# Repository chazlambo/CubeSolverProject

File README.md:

# CubeSolver

A self-contained Rubik's Cube solving robot: six stepper-driven faces, two servo
grippers on a moving ring, eighteen color sensors, an on-board Kociemba
two-phase solver, and a 320×240 display. Scan, solve, execute — no PC involved.

Everything here is one person's design: mechanical (SolidWorks), electrical
(KiCad), and firmware (Teensy 4.1).

---

## Status

**Working:** full autonomous scan → solve → execute cycle, driven from the
panel menu: the five Modes (Scramble Solve, Idle, Demo, Step Solve, Patterns),
on-panel tuning with defaults in source and overrides in EEPROM, a hardware jog
page, live sensor diagnostics, an EEPROM fault log and lifetime stats. The
display stays live during scan and solve, the abort chord works throughout,
encoder faults are detected and handled, a scan is validated piece-by-piece
with automatic repair, and color classification carries a per-sensor
confidence.

**Known unfinished:**
- `VirtualCube::rebuildFromCubeArray()` — still labeled `UNFINISHED NEEDS
  DEBUGGING` in its header, but the body is live and the firmware now relies
  on it (Cube State and pattern completion refresh the color array through
  it). The stale part is the label, not the code; it has no rollback on
  failure, which no current caller needs.
- Color sensor board 2, sensor 2 has a **dead green channel** — it reads exactly
  `0` for all six sticker colors in every archived calibration run. The firmware
  now detects this (`ColorSensor::checkSensorHealth`) but it is a hardware fault.
- Face steppers run without an acceleration ramp (`MultiStepper` is constant
  speed by design). Left as-is deliberately — a ramp would slow the solve.

---

## Which sketch do I flash?

**`Code/Main Code/CubeSolver/CubeSolver.ino`** — that's the program.

Everything under `Code/Test Code/` is bring-up and calibration tooling. The ones
still worth keeping:

| Sketch | Purpose |
|---|---|
| `Test Code/Bench_Tune` | Headless Serial protocol for scripted tuning: moves, parameters, every encoder before/after each move. Driven by `Code/tools/bench.py` |
| `Test Code/Actuator_Test` | Serial menu for manual moves and jam-recovery testing |
| `Test Code/Test_Motor_Calibrate` | Motor encoder calibration (also Settings → Calibration → Motor Positions) |
| `Test Code/Test_Color_Calibrate` | Color calibration (also Settings → Calibration → Color Sensors) |
| `Test Code/I2C_Search` | Bus scanner — genuinely useful on a five-mux rig |
| `Test Code/Test_Menu` | Menu, wheel and panel bench test — see below |

**`Test Code/Test_Menu`** drives the same `CubeMenu` and `CubeDisplay` the
firmware does, so anything that feels wrong there feels wrong in the firmware.
It runs no scan, solve or calibration. It does move real hardware from three
places: **Load** / **Eject**, the **Actuators** page (every servo and ring
position, each face motor and both whole-cube rotations, one part at a time),
and Diagnostics → Tuning → Servos, which drives a horn to each value as you
dial it. Everything under `Screens` is drawing only.

It also carries a `Screens` submenu that draws each operation screen (scan step
rows, calibration color chips, the solve progress bar, the error look) from
canned data, so the panel can be judged and photographed in seconds instead of
by running a 40-second scan to check one label. `Input Report` is a live
readout of the wheel count and every button — the fastest way to spot a flaky
encoder or a dead button.

It runs in the simulator too, with no machine at all:

```sh
cmake -S Code/sim -B Code/sim/build-test -DSIM_SKETCH=Test_Menu
cmake --build Code/sim/build-test -j && ./Code/sim/build-test/cubesim
```

`Test Code/_Archive/` does not compile against the current tree (it includes a
`Cube.h` that no longer exists). Git history is the archive.

---

## Build

**Board:** Teensy 4.1. Not a 4.0 — the solver's lookup tables alone are 4.14 MiB,
which is 214% of a 4.0's flash, and pins 40/41 don't exist on a 4.0.

**Toolchain:** Arduino IDE + Teensyduino.

> **TODO:** record the exact Arduino IDE and Teensyduino versions you build with,
> plus CPU speed and USB type from the Tools menu.

**Sketchbook layout — this is the non-obvious step.** `Code/libraries/` is an
Arduino *sketchbook libraries* folder, and the build must compile the repo's
copy, not a stale one. Two working setups:

1. **Point the sketchbook at the repo:** set Arduino's sketchbook location to
   the `Code/` directory (File → Preferences → Sketchbook location). Then
   `#include <CubeSystem.h>` and `#include <kociemba.h>` resolve, and
   `lv_conf.h` is found automatically.
2. **Link from the default sketchbook** (what this machine actually does —
   the sketchbook stays at `Documents/Arduino` so Library Manager installs
   land in the usual place):
   - `Documents/Arduino/libraries/CubeSolver` → symlink to
     `Code/libraries/CubeSolver`
   - `Documents/Arduino/libraries/kociemba` → junction to
     `Code/libraries/kociemba`
   - `Documents/Arduino/libraries/lv_conf.h` → a one-line forwarder header
     that does `#include "../../Projects/Cube_Solver/Code/libraries/lv_conf.h"`

Either way, do **not** copy the libraries into the sketchbook — you'll edit
the repo and build a stale copy. And never place an `lv_conf.h` inside the
`lvgl` library folder itself: if lvgl's own directory ever lands on the
include path, `__has_include("lv_conf.h")` silently builds the whole project
against that copy instead of the repo's.

### Dependencies

None of these are vendored except Kociemba. Install via Library Manager unless
noted.

| Library | Source | Notes |
|---|---|---|
| AccelStepper | Library Manager / airspayce.com | GPL-2.0 |
| MultiStepper | ships inside AccelStepper | constant-speed by design |
| PWMServo | bundled with Teensyduino | Teensy-only; **not** the stock `Servo` |
| TCA9548 | RobTillaart/TCA9548 | I²C multiplexer |
| veml6040 | ThingPulse/VEML6040 | color sensors |
| RunningMedian | RobTillaart/RunningMedian | scan filtering |
| Adafruit_seesaw | Adafruit | ANO scroll-wheel breakout |
| ILI9341_T4 | vindar/ILI9341_T4 (GitHub) | Teensy-4-specific DMA driver |
| LVGL | lvgl/lvgl | **v9.x** — the code uses v9-only APIs |
| EEPROM / Wire | Teensyduino core | two I²C buses used |
| SPI | Teensyduino core | pulled in transitively by ILI9341_T4, not included directly |
| kociemba | **vendored** at `Code/libraries/kociemba/` | from vindar/kociemba |

> **TODO:** pin the versions you actually build against, especially LVGL — the
> code uses `lv_display_create` / `lv_tick_set_cb`, which are v9-only.

### Menu theme assets

The menu's look is generated, not hand-drawn. `docs/theme/` holds the design as
two HTML files, and `Code/tools/bake_theme.py` rasterizes *those same files*
through headless Chrome at the panel's native 320x240, then packs the result
into LVGL C arrays under `Code/libraries/CubeSolver/utility/`:

```sh
python3 Code/tools/bake_theme.py              # images + fonts (needs network)
python3 Code/tools/bake_theme.py --no-fonts   # images only
```

The generated files **are committed**, so a normal build needs none of this —
run it only after changing the design. It needs `google-chrome`, `python3-pil`,
and `npx` for the font conversion.

Two things about those assets are load-bearing and easy to undo by accident:

- **They live in `utility/`.** `Code/libraries/CubeSolver` has no
  `library.properties`, so the Arduino IDE treats it as a 1.0-format library and
  compiles only the library root and `utility/`. Assets moved to a prettier
  subdirectory are silently not compiled, and the sketch fails to link.
- **The recolorable masks are RGB565A8, not A8.** LVGL reads an uncompressed
  RGB565A8 straight out of flash, but copies every alpha-only image into RAM
  first. The frame band alone is 49 KB — bigger than the 32 KB pool of the
  time, and most of today's 64 KB — so as A8 it fails to allocate, and with
  `LV_USE_LOG` at 0 it fails *silently*, drawing nothing at all. This costs
  about 220 KB of flash and is worth it.

Total asset cost: **~565 KB of flash**, against the ~3.3 MB left after the
solver's own 4.14 MiB of lookup tables. RAM is unchanged.

### lv_conf.h

`Code/libraries/lv_conf.h` is **required** and its settings are not defaults.
`LV_COLOR_DEPTH 16` must match what ILI9341_T4 expects; a mismatch does not fail
to build, it renders wrong colors and looks like a hardware fault. See the
comments in that file for the load-bearing settings.

**`LV_MEM_SIZE` is 64 KB, and running out of it hangs the machine.**
`LV_USE_ASSERT_MALLOC` is 1 and LVGL's default assert handler is `while(1);`, so
an exhausted pool is not a degraded UI — it is a halt, with no message, because
`LV_USE_LOG` is 0. It started at 32 KB, which the themed menu alone came within
~1 KB of; the operation screens took the peak to ~27 KB and the firmware hung
at boot with no output at all, so it went to 48 KB. The Sensor Test chips then
took the widget set to 35 KB and tripped the boot warning below, so it went to
64 KB. Every raise was set against a measurement, not a guess.

Two things watch this now: `CubeDisplay::begin()` prints the pool usage over
Serial once every widget exists, and warns below 8 KB free; and `M` in the
desktop simulator prints it live. Check the boot line before assuming a new
screen is free.

---

## Wiring

Verified against the `TEENSY_4.1` footprint's pad-to-net mapping in
`Circuitry/KiCad/Cube Solver/Motherboard/Motherboard.kicad_pcb`.
`Code/libraries/CubeSolver/CubeHardwareConfig.cpp` is the single source of truth
in firmware.

| Pin | Signal | Pin | Signal |
|---:|---|---:|---|
| 0 / 1 | U step / dir | 18 / 19 | **I²C0** SDA / SCL |
| 2 / 3 | R step / dir | 22 / 23 | Bottom / Top servo |
| 4 / 5 | F step / dir | 24 / 25 | B step / dir |
| 6 / 7 | D step / dir | 26 | Stepper enable (all 7) |
| 8 / 9 | L step / dir | 28 / 29 | Ring step / dir |
| 10 | Display DC | 30 | Encoder mux /RESET |
| 11 / 12 | Display MOSI / MISO | 32 | Power sense |
| 13 | Display SCK (+ onboard LED) | 40 / 41 | Color LED 2 / 1 |
| 14 / 15 | Display CS / RESET | 16 / 17 | **I²C1** SCL / SDA — see note |

**I²C addresses**

| Addr | Device | Bus |
|---|---|---|
| `0x70` | TCA9548 — encoder mux (7 AS5600 behind it) | Wire |
| `0x74`–`0x75` | TCA9548 ×2 — color board 1 | Wire |
| `0x76`–`0x77` | TCA9548 ×2 — color board 2 | Wire |
| `0x36` | AS5600 magnetic encoder ×7 | Wire (behind mux) |
| `0x10` | VEML6040 ×18 | Wire (behind muxes) |
| `0x49` | Adafruit seesaw (ANO wheel) | **Wire1** |

No pin or address conflicts.

### ⚠ Known board/firmware divergence

The firmware puts the scroll wheel on **Wire1 (pins 16/17)**, but Motherboard
Rev A routes connector J17 to **Wire0 (pins 18/19)**, and Teensy pads 16/17 are
marked unconnected. Since the machine works, there must be a bodge wire.

> **TODO:** confirm the bodge and either roll it into a Rev B or note it on the
> board. Right now this exists only in the hardware and in your head.

- **The color scanner is mounted rotated 90° from its original layout.** It
  was turned in CAD to make the assembly fit, which changed which faces each
  scan pass reads — from `[L,B] [U,F] [D,R]` to
  `[Back,Right] [Left,Down] [Up,Front]` — and **no firmware changed**, because
  `scanCube()` identifies each face from its own centre color rather than
  assuming which one it is looking at. What the design does rely on is the two
  sensors' position *relative to each other*, and rotating the whole assembly
  preserves that. Moving one sensor relative to the other would not, and would
  break `left1`/`left2` in `scanCube()`.

  The only thing tracking the physical order is `kScanPassFaces` in
  `CubeOpShape.cpp`, which fills the panel's face row during a scan. Rotate the
  scanner again and that table is the one thing to update.

Two other things worth knowing:
- **Pin 10 must be the display DC.** ILI9341_T4 drives DC through the SPI
  peripheral's chip-select logic during DMA, so it has to be a hardware CS pin —
  on Teensy 4.1 SPI0 that's 10, 36 or 37. A plain GPIO fails confusingly.
- Pins 24/25 are Teensy's `Wire2`, consumed by the B stepper. There is **no third
  I²C bus available** without moving that motor.

---

## First run

Order matters — the solver needs both calibrations, and color calibration needs
motors that already home correctly.

### 1. Motor encoder calibration

Menu → **Settings → Calibration → Motor Positions**, or flash
`Test Code/Test_Motor_Calibrate`.

Records four encoder positions per motor, one per quarter turn, into EEPROM.

> **TODO:** describe the physical setup — how the fingers should be positioned
> relative to the cube before starting, what a good result looks like, and when
> this needs redoing after a mechanical change.

### 2. Color calibration

Menu → **Settings → Calibration → Color Sensors**, or flash
`Test Code/Test_Color_Calibrate`.

Needs a **solved** cube. Steps through orientations recording a reference RGBW
per color per sensor, plus an "empty chamber" reference.

The firmware now derives a per-sensor decision threshold from this data
(`ColorSensor::computeSeparations`) rather than using one global tolerance, so a
bad calibration degrades classification measurably. Check the health report.

> **TODO:** describe ambient lighting conditions, whether the lid should be on,
> and how to tell a good calibration from a marginal one.

### 3. Servo endpoints

Menu → **Settings → Calibration → Servo Positions**. Rows preview live as the
wheel turns, behind a red confirm; values persist in the tuning EEPROM block.

The compiled defaults live in the shared parameter table
(`Code/libraries/CubeSolver/CubeTuneTable.cpp`), not in
`CubeHardwareConfig.cpp` — the `topExtPos` / `botExtPos` globals there are read
once at servo construction and then overridden at boot by the table, so editing
them no longer changes the machine.

> **TODO:** record how the defaults were determined and how to retune after
> changing a servo horn or linkage.

---

## Operating

1. Power on. The machine homes its motors if calibrated.
2. Turn the wheel to **Load & Scan Cube**, press SELECT.
3. Insert a scrambled cube, press SELECT. It scans (~25–40 s) and the main
   menu becomes **Cube Ready**.
4. Select **Solve**, press SELECT. It computes and reports the move count.
5. Press SELECT to execute (LEFT cancels and leaves the cube as it is).

**Abort:** hold SELECT and LEFT together for 1.5 s during a scan or solve. The
machine stops at the next mechanically safe point, releases the cube, and
returns to the menu.

**On any error that can leave the machine holding the cube, it is released
automatically** — the solve paths and the abort paths all route through
`safeStop()`. Scan-time color and build errors do not, because at those points
the ring and both servos are already retracted.

### Error codes

| Range | Meaning |
|---|---|
| Scan 1–3 | A sensor could not identify a face, or two faces read the same |
| Scan 1X/2X | Sensor 1/2's face was rejected when set on the virtual cube |
| Scan 3X | Could not determine orientation |
| Scan 41 | Fewer than six distinct faces set — a duplicate-centre misread |
| Scan 42-47 | Wrong number of some color (not nine of each) |
| Scan 5X | Could not build the cube array |
| Scan 60 | Physically impossible cube, auto-repair failed → rescan |
| Scan 70 | Aborted by user |
| Scan 80 / 81 | Reorientation move ROTX / ROTZ failed (encoder fault) |
| Scan 90 | A color sensor board failed to initialise at boot |
| Scan 91 | Motors failed to home before the first clamp (jam / encoder fault) |
| Cal 82 | A calibration reorientation move failed |
| Solve 11 | Cube not scanned yet |
| Solve 12 | No solution — illegal cube or solver timeout |
| Solve 13 | Centres not canonical → **orientation** was misread |
| Solve 14 | Impossible piece → a **color** was misread → rescan |
| Solve 15 | Solution longer than the move buffer |
| Exec 105 / 125 | Aborted by the user (between moves / inside a move) |
| Exec 1XX | A move failed; cube released and virtual state invalidated |
| Move 3 / 21 / 22 / 24 / 25 | Raw move (Modes, jog): invalid token / motors not calibrated / jam or align timeout / encoder unreadable / aborted |
| Move 1X | Virtual move failed — rescan |
| Cal 8 | Color calibration failed to save — machine is **not** calibrated |
| Cal 9 | Color calibration aborted; EEPROM left untouched |

The raw-move codes appear on the panel when a scramble, idle turn, pattern
fold or jogged move fails, and in the Fault Log under the Mode and Jog
sources.

Code 14 and 60 both mean "the cube I think I have cannot exist" — the fix is a
rescan, not a retry.

**Code 13 is effectively unreachable, by design.** `buildCubeArray()` relabels
colors through the reported orientation, so the centres come out canonical
whatever that orientation was. A *misread* orientation therefore produces a
different but internally consistent cube that is legal, piece-valid and
solvable — the machine would execute ~20 moves in the wrong frame with no error
at any layer. The centre check is kept as cheap insurance against a corrupted
`cubeArray`; detecting an orientation misread needs a cross-check against
something outside the cube model and is **not currently implemented**.

---

## Repo layout

```
3D Models/      SolidWorks parts and assemblies, plus print-ready STLs
Circuitry/      KiCad projects: Motherboard, Motor Breakout, Color Sensor
Code/
  Main Code/CubeSolver/   <- THE PROGRAM
  Test Code/              bring-up and calibration sketches
  libraries/
    lv_conf.h             required LVGL config (see above)
    CubeSolver/           the machine's own code
    kociemba/             vendored solver (from vindar/kociemba)
```

`.gitignore` excludes regenerable KiCad output (auto-backup zips, footprint
caches, per-user project state) and SolidWorks lock files. `.gitattributes`
marks binary CAD/fab formats `-text` so git's heuristic can't CRLF-mangle them.

---

## Notes for future-you

- **The alignment step sign lives in one place.** `CubeSystem::kAlignStepSign`.
  Both closed-loop routines use `encError()`; if alignment ever drives away from
  target, flip that constant and nothing else.
- **Encoder reads can fail.** `MotorEncoder::scanChecked()` returns negative on
  I²C failure and every control path treats that as a fault, not a position.
  Never go back to raw `scan()` in a control loop.
- **`pumpDelay()` instead of `delay()`** anywhere that waits more than a few ms,
  so the display and abort keep working.
- **The panel is driven synchronously, on purpose.** `CUBE_DISPLAY_ASYNC_DMA`
  in `CubeDisplay.h` is 0: every LVGL flush is written straight to the glass
  and returns when it is on the wire. The driver's async DMA/differential mode
  (mode 1) is faster, but on this board it left the glass holding the previous
  frame in large chunks, or coloured snow, while the driver believed the new
  one had been sent — and because that mode only ever re-sends pixels it thinks
  changed, the damage stayed until something drew over it. The header comment
  has the history. `cubeDisplay.repaintAll()` re-sends every pixel; the sketch
  calls it at the end of boot and on every return to the menu. In mode 1 never
  use `tft->update(internal_fb)` for that: handed its own buffer the driver
  rotates it onto itself.
- **A white panel heals itself now.** On the same marginal wire, a corrupted
  byte during a heavy flush can land in the panel's command slot — `RAMWR`
  (0x2C) and `CASET` (0x2A) are each one flipped bit from `DISPOFF` (0x28) —
  and a panel that latches `DISPOFF`/`SLPIN`/`SWRESET` shows solid white,
  which no amount of pixel drawing repairs. `CubeDisplay::panelHealthTick()`
  (run from every `update()`) re-sends `DISPON`+`SLPOUT` each second and
  re-runs the full init when the self-diagnostic register reads wrong, so a
  white-out lasts about a second instead of until power-cycle. It prints
  `Display: panel lost its init (recovery #N)` on Serial; that count climbing
  while scrolling is the wire talking.
- Solve times: Kociemba runs from flash. `set_memory()` would be ~4× faster but
  the 479 KiB buffer doesn't fit alongside the display's ~200 KB of RAM2.

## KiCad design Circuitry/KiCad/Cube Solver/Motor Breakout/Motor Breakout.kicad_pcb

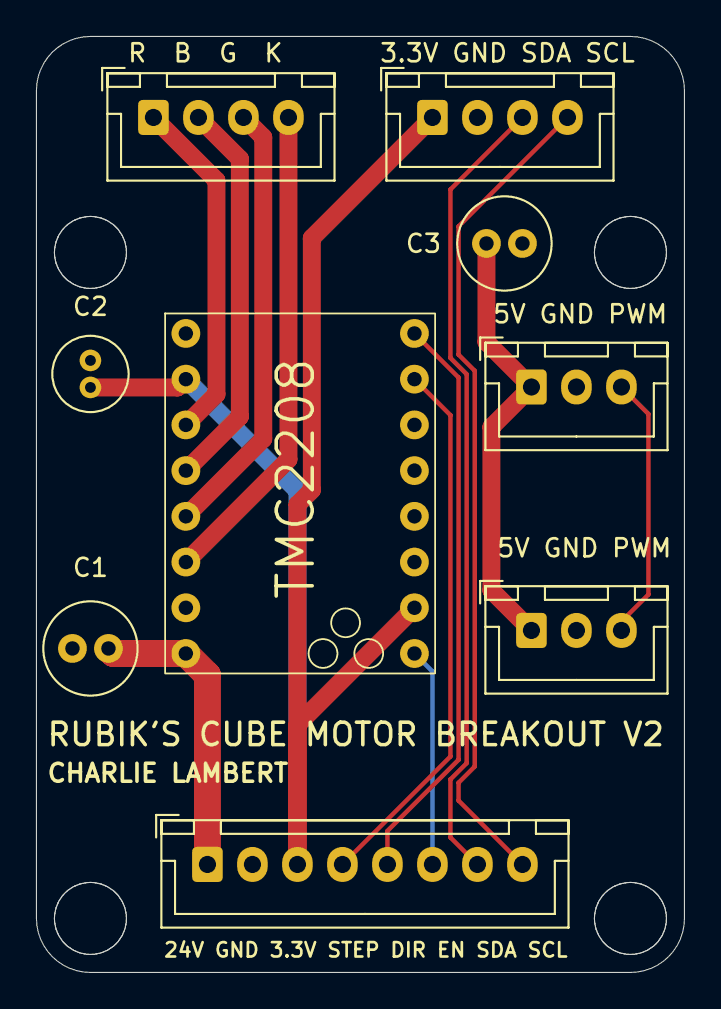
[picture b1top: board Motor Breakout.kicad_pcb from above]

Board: 2 copper layers, 36.0 x 52.0 mm, 9 parts (0 on the bottom side), 14 nets.

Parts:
C1, C3: 100µF; C_Radial_D5.0mm_H11.0mm_P2.00mm
C2: 0.1µF; C_Radial_D4.0mm_H7.0mm_P1.50mm
J2: Motor Input; JST_XH_B4B-XH-A_1x04_P2.50mm_Vertical
J3: Motherboard Breakout; JST_XH_B8B-XH-A_1x08_P2.50mm_Vertical
J4: Servo Input; JST_XH_B3B-XH-A_1x03_P2.50mm_Vertical
J5: Servo Output; JST_XH_B3B-XH-A_1x03_P2.50mm_Vertical
J6: Encoder Input; JST_XH_B4B-XH-A_1x04_P2.50mm_Vertical
U1: TMC2208_Breakout

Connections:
+3.3V: C2.2, J3.3 (3.3V), J6.1 (VCC), U1.2 (VIO), U1.15 (MS1)
+5V: C3.1, J4.1 (5V), J5.1 (5V)
+24V: C1.1, J3.1 (24V), U1.8 (VMOT)
/Black: J2.4 (Black), U1.6 (M2B)
/Blue: J2.2 (Blue), U1.4 (M2A)
/Green: J2.3 (Green), U1.5 (M1A)
/Red: J2.1 (Red), U1.3 (M2B)
DIR: J3.5 (DIR), U1.9 (DIR)
EN: J3.6 (EN), U1.16 (EN)
GND: C1.2, C2.1, C3.2, J3.2 (GND), J4.2 (GND), J5.2 (GND), J6.2 (GND), U1.1 (GND), U1.7 (GND)
PWM: J4.3 (Signal), J5.3 (Signal)
SCL: J3.8 (SCL), J6.4 (SCL)
SDA: J3.7 (SDA), J6.3 (SDA)
STEP: J3.4 (STEP), U1.10 (STEP)

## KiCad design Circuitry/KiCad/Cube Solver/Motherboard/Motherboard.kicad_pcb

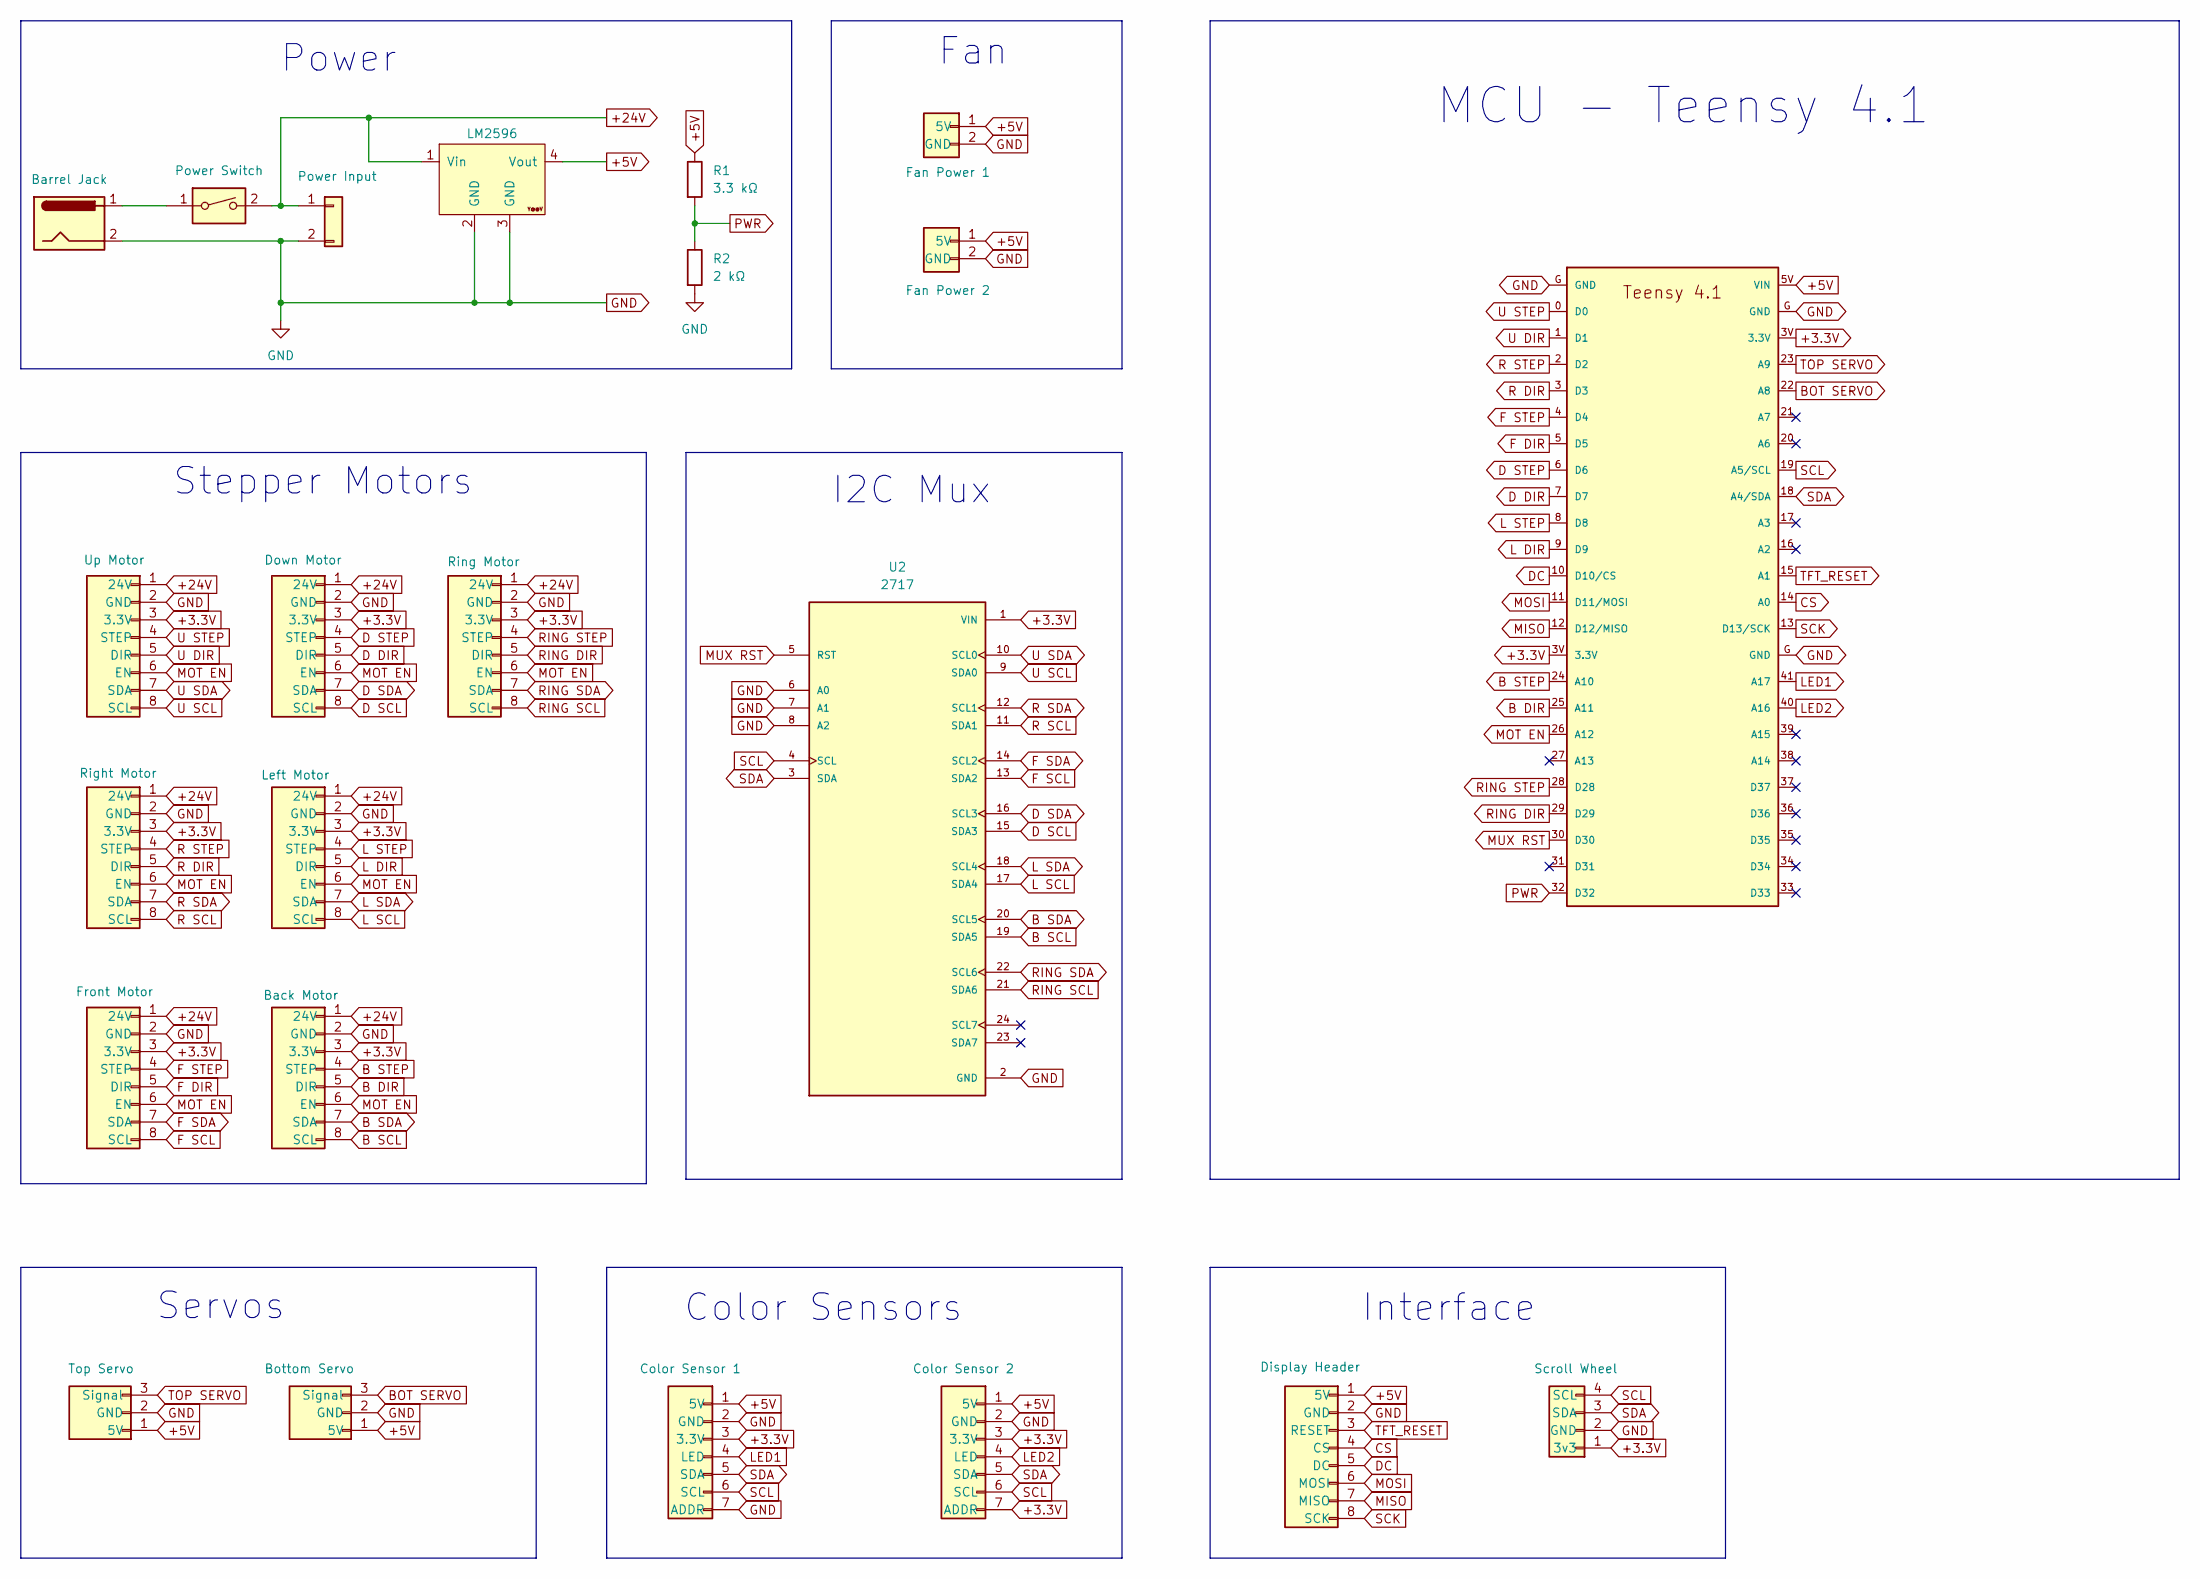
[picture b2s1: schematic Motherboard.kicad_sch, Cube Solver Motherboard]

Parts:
A1: TEENSY_4.1
J1: Color Sensor 1; JST_XH_B7B-XH-A_1x07_P2.50mm_Vertical
J2: Color Sensor 2; JST_XH_B7B-XH-A_1x07_P2.50mm_Vertical
J3: Top Servo; JST_XH_B3B-XH-A_1x03_P2.50mm_Vertical
J4: Bottom Servo; JST_XH_B3B-XH-A_1x03_P2.50mm_Vertical
J5: Up Motor; JST_XH_B8B-XH-A_1x08_P2.50mm_Vertical
J6: Down Motor; JST_XH_B8B-XH-A_1x08_P2.50mm_Vertical
J7: Ring Motor; JST_XH_B8B-XH-A_1x08_P2.50mm_Vertical
J8: Right Motor; JST_XH_B8B-XH-A_1x08_P2.50mm_Vertical
J9: Left Motor; JST_XH_B8B-XH-A_1x08_P2.50mm_Vertical
J10: Back Motor; JST_XH_B8B-XH-A_1x08_P2.50mm_Vertical
J11: Front Motor; JST_XH_B8B-XH-A_1x08_P2.50mm_Vertical
J12: Barrel Jack
J13: Display Header; JST_XH_B8B-XH-A_1x08_P2.50mm_Vertical
J14: Power Input; AMASS_XT60-M_1x02_P7.20mm_Vertical
J15: Fan Power 1; JST_XH_B2B-XH-AM_1x02_P2.50mm_Vertical
J16: Fan Power 2; JST_XH_B2B-XH-AM_1x02_P2.50mm_Vertical
J17: Scroll Wheel; JST_XH_B4B-XH-A_1x04_P2.50mm_Vertical
R1: 3.3 kΩ; R_Axial_DIN0207_L6.3mm_D2.5mm_P10.16mm_Horizontal
R2: 2 kΩ; R_Axial_DIN0207_L6.3mm_D2.5mm_P10.16mm_Horizontal
SW1: Power Switch
U1: LM2596; YAAJ_DCDC_StepDown_LM2596
U2: 2717; MODULE_2717; PARTREV Sep 11, 2015

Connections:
+3.3V: A1.3V (3.3V), J1.3 (3.3V), J2.3 (3.3V), J2.7 (ADDR), J5.3 (3.3V), J6.3 (3.3V), J7.3 (3.3V), J8.3 (3.3V), J9.3 (3.3V), J10.3 (3.3V), J11.3 (3.3V), J17.1 (3v3), U2.1 (VIN)
+5V: A1.5V (VIN), J1.1 (5V), J2.1 (5V), J3.1 (5V), J4.1 (5V), J13.1 (5V), J15.1 (5V), J16.1 (5V), R1.1, U1.4 (Vout)
+24V: J5.1 (24V), J6.1 (24V), J7.1 (24V), J8.1 (24V), J9.1 (24V), J10.1 (24V), J11.1 (24V), J14.1, SW1.2, U1.1 (Vin)
B DIR: A1.25 (A11), J10.5 (DIR)
B SCL: J10.8 (SCL), U2.19 (SDA5)
B SDA: J10.7 (SDA), U2.20 (SCL5)
B STEP: A1.24 (A10), J10.4 (STEP)
BOT SERVO: A1.22 (A8), J4.3 (Signal)
CS: A1.14 (A0), J13.4 (CS)
D DIR: A1.7 (D7), J6.5 (DIR)
D SCL: J6.8 (SCL), U2.15 (SDA3)
D SDA: J6.7 (SDA), U2.16 (SCL3)
D STEP: A1.6 (D6), J6.4 (STEP)
DC: A1.10 (D10/CS), J13.5 (DC)
F DIR: A1.5 (D5), J11.5 (DIR)
F SCL: J11.8 (SCL), U2.13 (SDA2)
F SDA: J11.7 (SDA), U2.14 (SCL2)
F STEP: A1.4 (D4), J11.4 (STEP)
GND: A1.G (GND), J1.2 (GND), J1.7 (ADDR), J2.2 (GND), J3.2 (GND), J4.2 (GND), J5.2 (GND), J6.2 (GND), J7.2 (GND), J8.2 (GND), J9.2 (GND), J10.2 (GND), J11.2 (GND), J12.2, J13.2 (GND), J14.2, J15.2 (GND), J16.2 (GND), J17.2 (GND), R2.2, U1.2 (GND), U1.3 (GND), U2.2 (GND), U2.6 (A0), U2.7 (A1), U2.8 (A2)
L DIR: A1.9 (D9), J9.5 (DIR)
L SCL: J9.8 (SCL), U2.17 (SDA4)
L SDA: J9.7 (SDA), U2.18 (SCL4)
L STEP: A1.8 (D8), J9.4 (STEP)
LED1: A1.41 (A17), J1.4 (LED)
LED2: A1.40 (A16), J2.4 (LED)
MISO: A1.12 (D12/MISO), J13.7 (MISO)
MOSI: A1.11 (D11/MOSI), J13.6 (MOSI)
MOT EN: A1.26 (A12), J5.6 (EN), J6.6 (EN), J7.6 (EN), J8.6 (EN), J9.6 (EN), J10.6 (EN), J11.6 (EN)
MUX RST: A1.30 (D30), U2.5 (RST)
unnamed: J12.1, SW1.1
PWR: A1.32 (D32), R1.2, R2.1
R DIR: A1.3 (D3), J8.5 (DIR)
R SCL: J8.8 (SCL), U2.11 (SDA1)
R SDA: J8.7 (SDA), U2.12 (SCL1)
R STEP: A1.2 (D2), J8.4 (STEP)
RING DIR: A1.29 (D29), J7.5 (DIR)
RING SCL: J7.8 (SCL), U2.21 (SDA6)
RING SDA: J7.7 (SDA), U2.22 (SCL6)
RING STEP: A1.28 (D28), J7.4 (STEP)
SCK: A1.13 (D13/SCK), J13.8 (SCK)
SCL: A1.19 (A5/SCL), J1.6 (SCL), J2.6 (SCL), J17.4 (SCL), U2.4 (SCL)
SDA: A1.18 (A4/SDA), J1.5 (SDA), J2.5 (SDA), J17.3 (SDA), U2.3 (SDA)
TFT_RESET: A1.15 (A1), J13.3 (RESET)
TOP SERVO: A1.23 (A9), J3.3 (Signal)
U DIR: A1.1 (D1), J5.5 (DIR)
U SCL: J5.8 (SCL), U2.9 (SDA0)
U SDA: J5.7 (SDA), U2.10 (SCL0)
U STEP: A1.0 (D0), J5.4 (STEP)

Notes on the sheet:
Fan
I2C Mux
Power
Color Sensors
Interface
Servos
Stepper Motors
MCU - Teensy 4.1

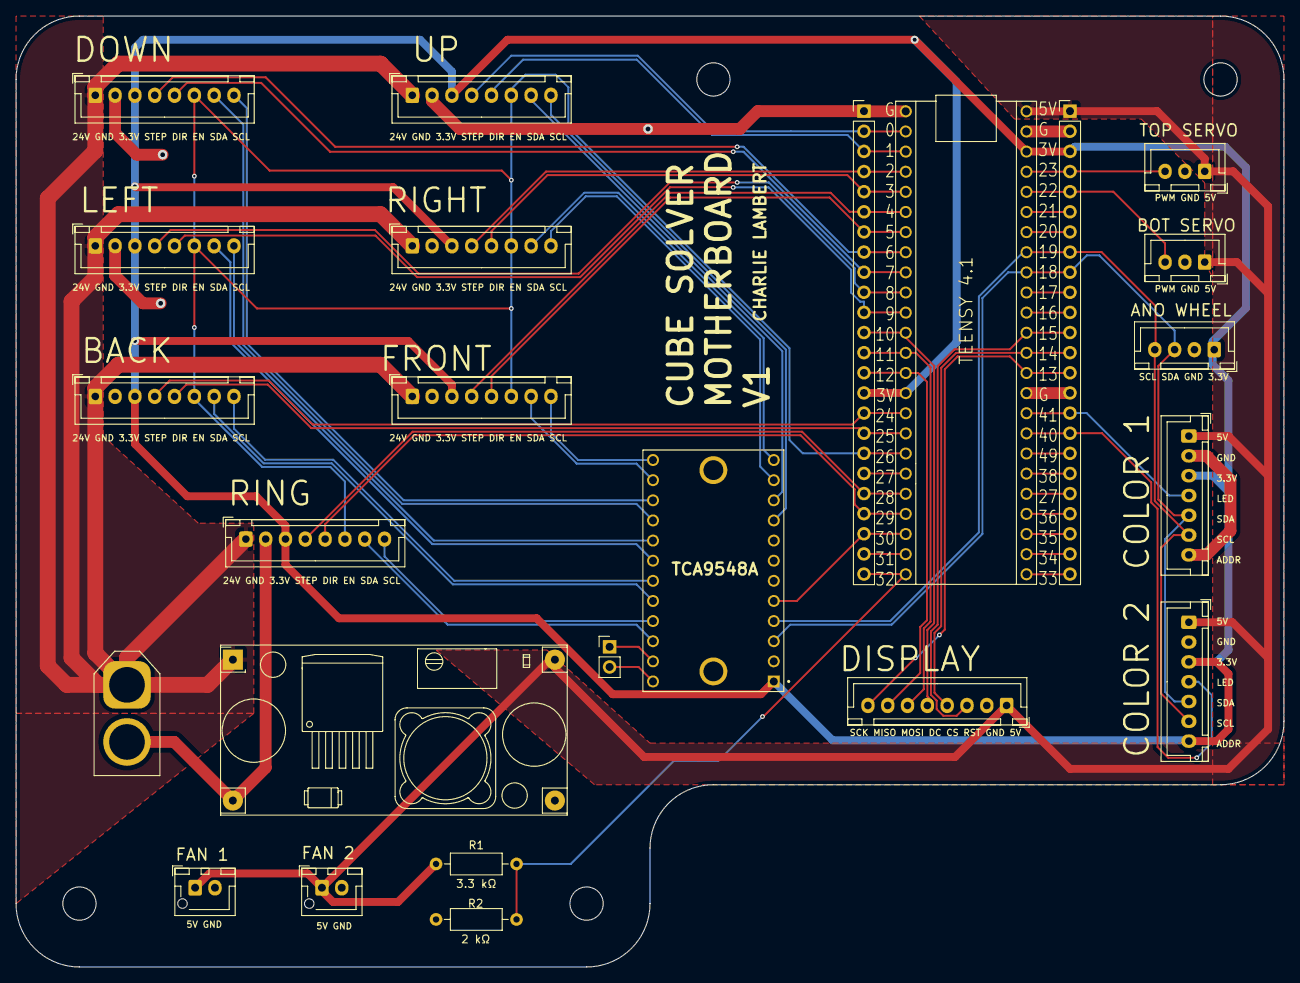
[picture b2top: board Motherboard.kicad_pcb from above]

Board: 2 copper layers, 160.0 x 120.0 mm, 21 parts (0 on the bottom side), 47 nets.

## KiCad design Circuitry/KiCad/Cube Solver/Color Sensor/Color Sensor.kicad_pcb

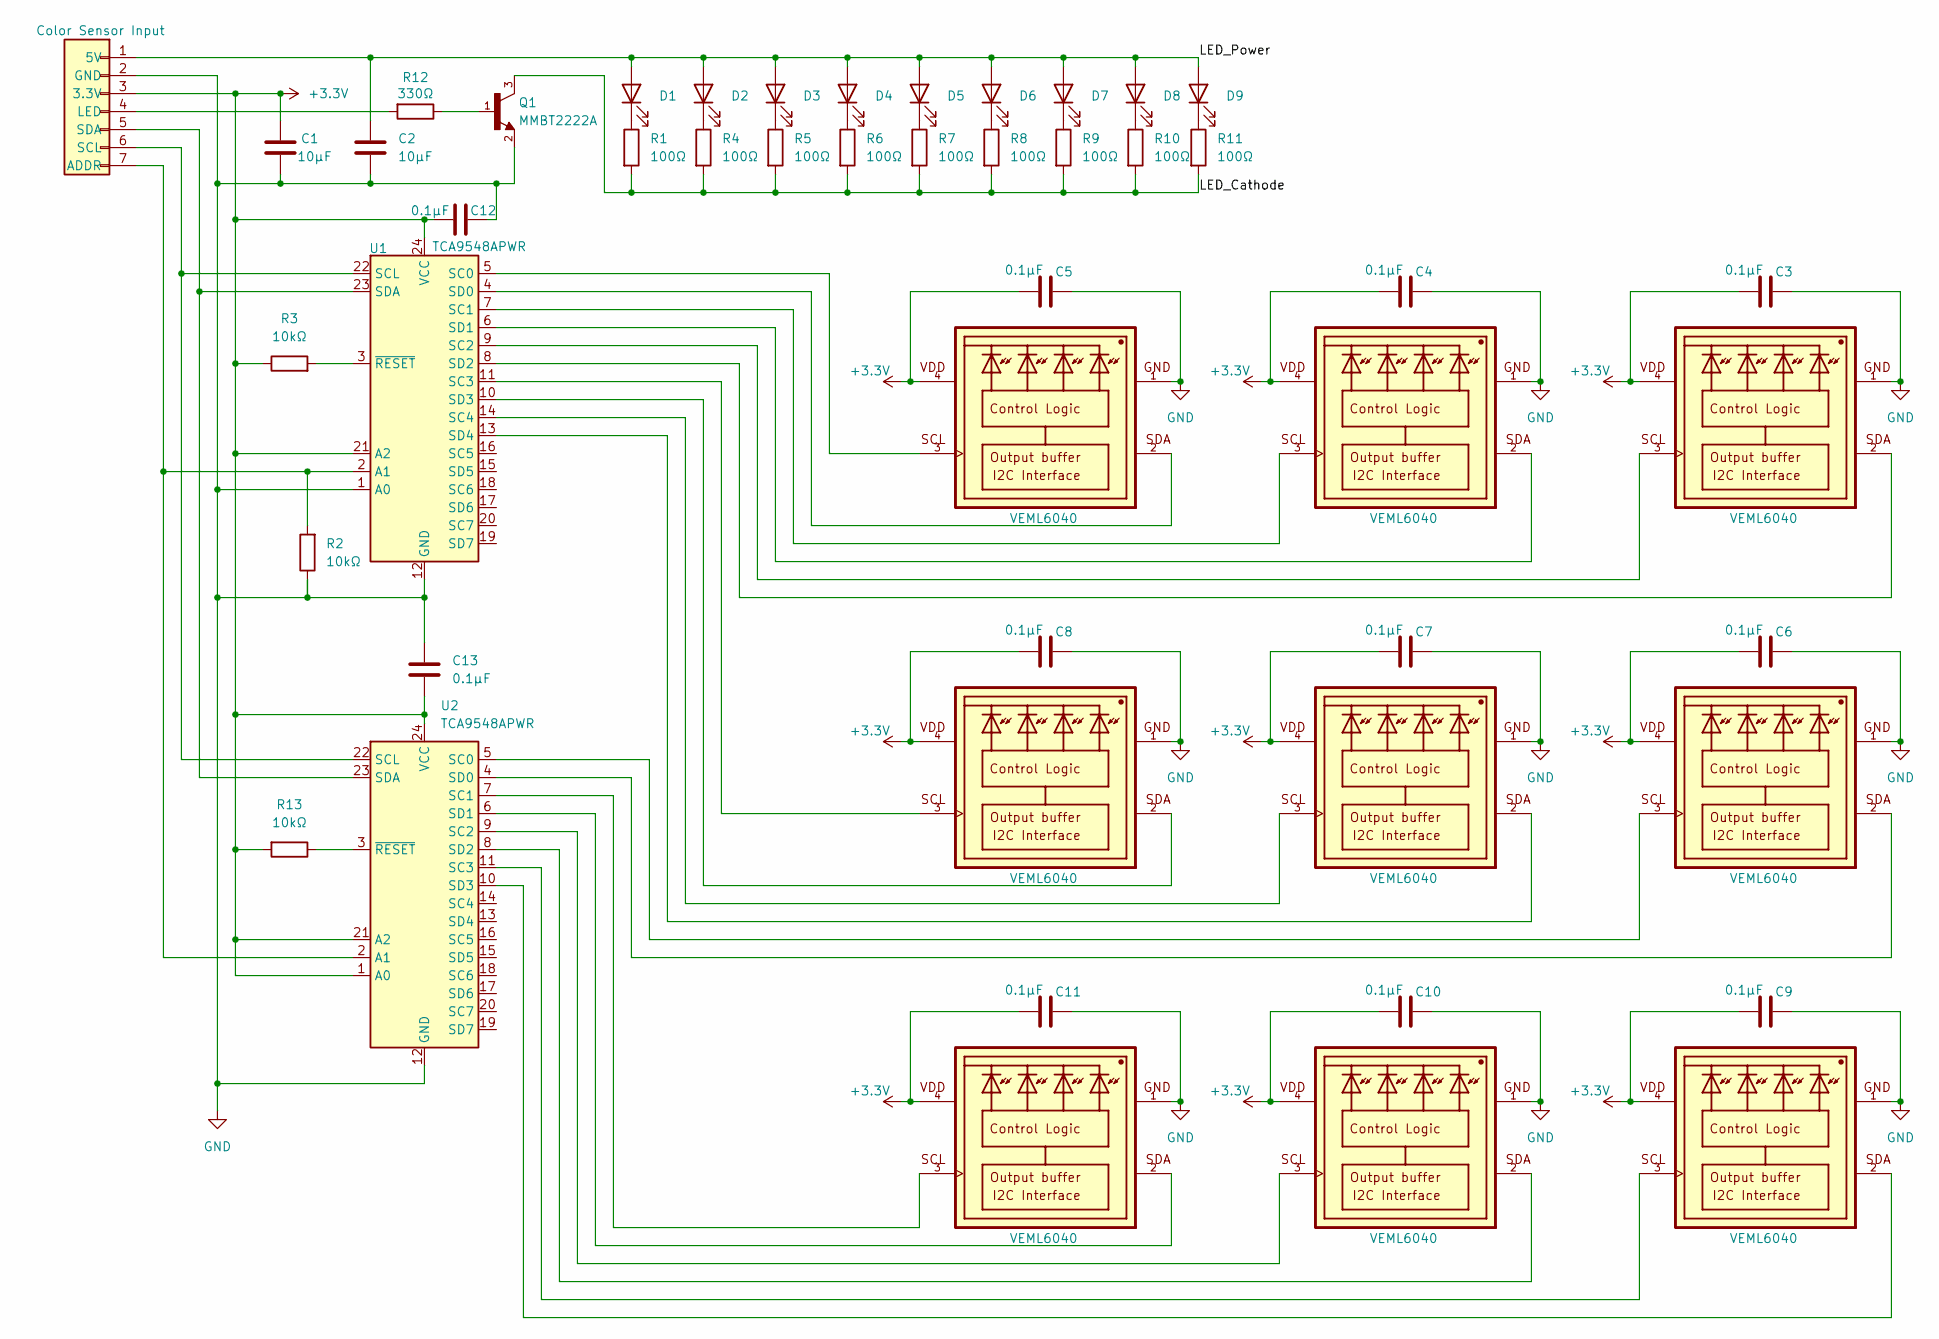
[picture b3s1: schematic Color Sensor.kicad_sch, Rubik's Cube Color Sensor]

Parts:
C1, C2: 10µF; C_0805_2012Metric
C3, C4, C5, C6, C7, C8, C9, C10, C11, C12, C13: 0.1µF; C_0805_2012Metric
D1, D2, D3, D4, D5, D6, D7, D8, D9: GW JTLMS3.GM-G6GV-XX55-1-60-R33; LED_PLCC_2835
J1: Color Sensor Input; JST_XH_S7B-XH-A-1_1x07_P2.50mm_Horizontal
Q1: MMBT2222A; SOT23
R1, R4, R5, R6, R7, R8, R9, R10, R11: 100Ω; R_0805_2012Metric
R2, R3, R13: 10kΩ; R_0805_2012Metric
R12: 330Ω; R_0805_2012Metric
U1, U2: TCA9548APWR; TSSOP-24_4.4x7.8mm_P0.65mm
U3, U4, U5, U6, U7, U8, U9, U10, U11: VEML6040; VISHAY_VEML6040_1.25X2X1

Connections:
+3.3V: C1.1, C3.2, C4.2, C5.2, C6.2, C7.2, C8.2, C9.2, C10.2, C11.2, C12.2, C13.2, J1.3 (3.3V), R3.1, R13.2, U1.21 (A2), U1.24 (VCC), U2.1 (A0), U2.21 (A2), U2.24 (VCC), U3.4, U4.4, U5.4, U6.4, U7.4, U8.4, U9.4, U10.4, U11.4
/LED_Cathode: Q1.3, R1.2, R4.2, R5.2, R6.2, R7.2, R8.2, R9.2, R10.2, R11.2
/LED_Power: C2.1, D1.2 (A), D2.2 (A), D3.2 (A), D4.2 (A), D5.2 (A), D6.2 (A), D7.2 (A), D8.2 (A), D9.2 (A), J1.1 (5V)
GND: C1.2, C2.2, C3.1, C4.1, C5.1, C6.1, C7.1, C8.1, C9.1, C10.1, C11.1, C12.1, C13.1, J1.2 (GND), Q1.2, R2.1, U1.1 (A0), U1.12 (GND), U2.12 (GND), U3.1, U4.1, U5.1, U6.1, U7.1, U8.1, U9.1, U10.1, U11.1
unnamed: D1.1 (K), R1.1
unnamed: D2.1 (K), R4.1
unnamed: D3.1 (K), R5.1
unnamed: D4.1 (K), R6.1
unnamed: D5.1 (K), R7.1
unnamed: D6.1 (K), R8.1
unnamed: D7.1 (K), R9.1
unnamed: D8.1 (K), R10.1
unnamed: D9.1 (K), R11.1
unnamed: J1.7 (ADDR), R2.2, U1.2 (A1), U2.2 (A1)
unnamed: J1.4 (LED), R12.2
unnamed: J1.6 (SCL), U1.22 (SCL), U2.22 (SCL)
unnamed: J1.5 (SDA), U1.23 (SDA), U2.23 (SDA)
unnamed: Q1.1, R12.1
unnamed: U1.5 (SC0), U5.3
unnamed: U1.7 (SC1), U4.3
unnamed: U1.9 (SC2), U3.3
unnamed: U1.11 (SC3), U8.3
unnamed: U1.14 (SC4), U7.3
unnamed: U1.4 (SD0), U5.2
unnamed: U1.6 (SD1), U4.2
unnamed: U1.8 (SD2), U3.2
unnamed: U1.10 (SD3), U8.2
unnamed: U1.13 (SD4), U7.2
unnamed: R3.2, U1.3 (~RESET)
unnamed: U2.5 (SC0), U6.3
unnamed: U2.7 (SC1), U11.3
unnamed: U2.9 (SC2), U10.3
unnamed: U2.11 (SC3), U9.3
unnamed: U2.4 (SD0), U6.2
unnamed: U2.6 (SD1), U11.2
unnamed: U2.8 (SD2), U10.2
unnamed: U2.10 (SD3), U9.2
unnamed: R13.1, U2.3 (~RESET)

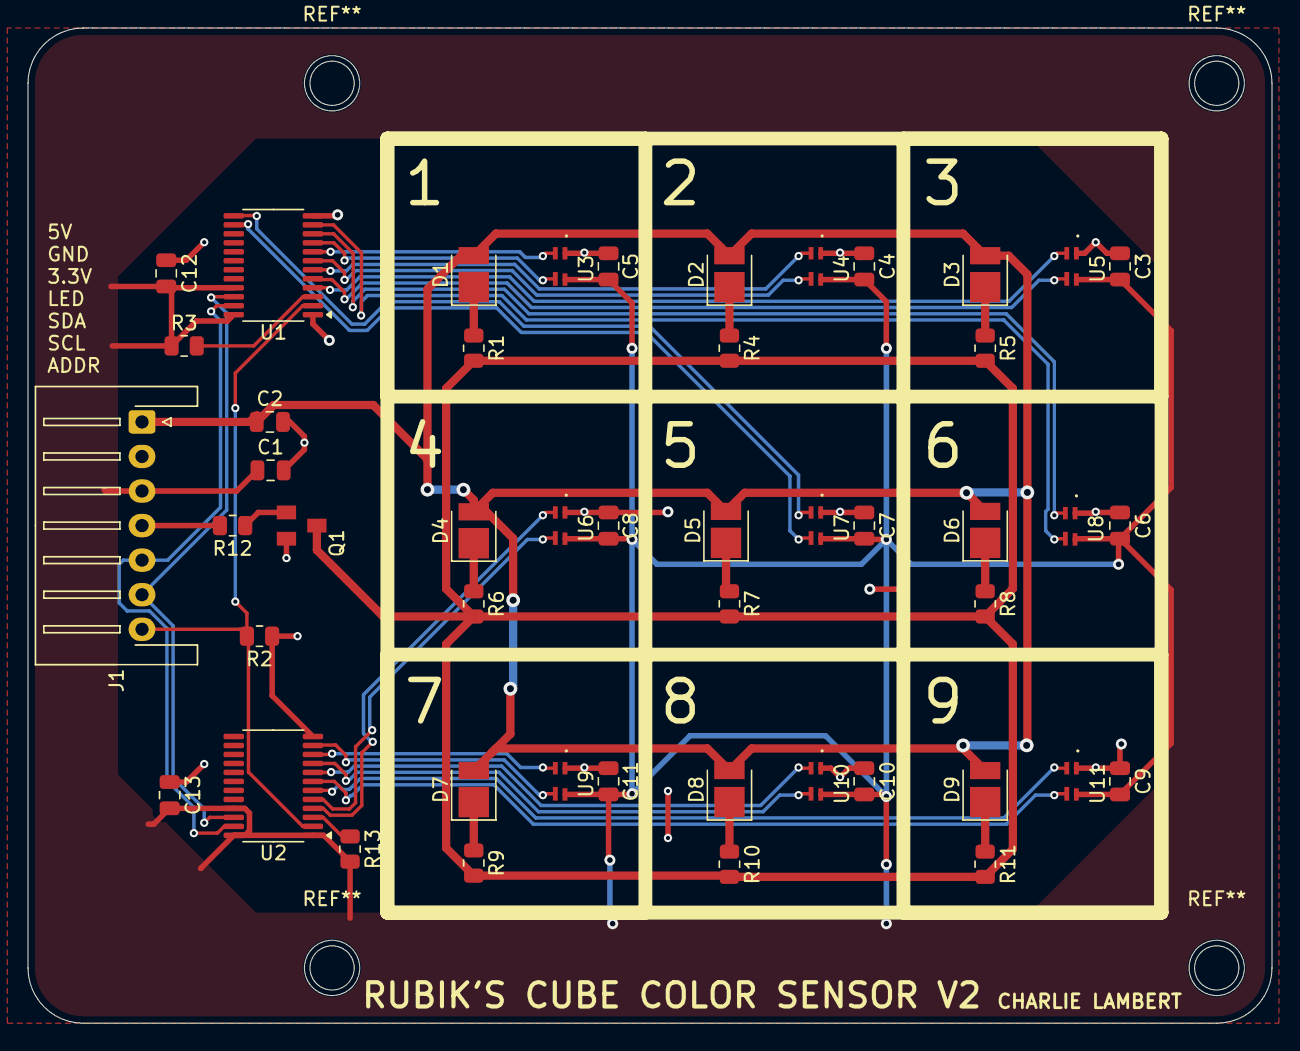
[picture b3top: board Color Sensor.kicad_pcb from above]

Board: 2 copper layers, 90.0 x 72.0 mm, 48 parts (0 on the bottom side), 38 nets.

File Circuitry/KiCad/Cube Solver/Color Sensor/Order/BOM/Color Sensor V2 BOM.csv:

"Id";"Designator";"Footprint";"Quantity";"Designation";"Supplier and ref";
1;"U4,U5,U6,U7,U8,U9,U10,U11,U3";"VISHAY_VEML6040_1.25X2X1";9;"VEML6040";;;
2;"D1,D5,D9,D7,D3,D2,D6,D4,D8";"LED_PLCC_2835";9;"GW JTLMS3.GM-G6GV-XX55-1-60-R33";;;
3;"C5,C11,C13,C7,C4,C10,C3,C6,C8,C9,C12";"C_0805_2012Metric";11;"0.1µF";;;
4;"R4,R6,R5,R10,R7,R11,R9,R1,R8";"R_0805_2012Metric";9;"100Ω";;;
5;"C1,C2";"C_0805_2012Metric";2;"10µF";;;
6;"U2,U1";"TSSOP-24_4.4x7.8mm_P0.65mm";2;"TCA9548APWR";;;
7;"R12";"R_0805_2012Metric";1;"330Ω";;;
8;"R2,R3,R13";"R_0805_2012Metric";3;"10kΩ";;;
9;"Q1";"SOT23";1;"MMBT2222A";;;
10;"J1";"JST_XH_S7B-XH-A-1_1x07_P2.50mm_Horizontal";1;"Color Sensor Input";;;

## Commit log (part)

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2023-10-17 Added files
2023-10-18 Actuator Test Fully Working
    Added menu and user select options
2023-10-21 New Top Bracket
    Updated top servo extended position and reduced steppers speed.
2023-10-21 Created CubeBuilder Test
2023-10-21 Added buildCubeArray Functionality
2023-10-21 Added full orientation support
    Can now build full cube with orientation properly working!!!!
2023-10-22 Code Cleanup + rotR Function
2023-10-23 Implemented Virtual Cube Rotation Functions
    Note: rebuild from cube array not functional as intended, does not currently rebuild cube just rewrites colorCubeArray
2023-10-23 Changed CubeBuilder to CubeSolveTest
    Included the kociemba solving library to test building, orienting, solving, and then rotating a scrambled cube to solution
2023-10-24 CubeSolveTest Working!
    It all works!!! Time to try to translate this to the motors!
2023-10-24 Added libraries folder and moved files accordingly
    Moved kociemba library to folder and made new library for the cube header and source files
2023-10-24 Started MultiStepper Testing
    Decided to work on parsing the solve string first though, will come back.
2023-10-25 Test Code for running MultiStepper
2023-10-25 Started String Parsing File
    Really weird errors though
2023-10-25 Made Archive, Added SimpleSolve
    SimpleSolve is very incomplete
2023-10-26 Added SimpleSolver and ScrambleSolver
2023-10-26 Fixed virtual cube library
2024-07-11 Mk.2 initial actuator testing
2024-07-18 Started sensors files
2024-07-18 Updated ADC Pin Table
2024-07-21 Removed folder structure, working on sensors
2024-07-22 Working on color sensors
2025-05-13 Updated library include structure
2025-05-14 Calibration working. Removed cube_basic
2025-05-14 Test Motor Calibrate
2025-05-14 Calibration Complete
    Yay it's working :)
2025-05-15 Servo Position Initialization
    Servos will now reset with a sweep if necessary.
2025-05-15 Started refactor
2025-05-15 Debugging pt1
2025-05-15 Actuator_Test Working
2025-05-15 Test_Motor_Calibrate working
2025-05-17 Updated virtual cube class.
2025-05-17 Added Hardware Config and CubeSystem Class
2025-05-18 Full motor pot calibration implemented
    Now calibrates all 4 values for motor positions.
2025-05-18 Cleaned up and and added comments
2025-05-19 Added logic to home motor to nearest calibrated 90deg angle
2025-05-19 Color Calibration (untested)
2025-05-19 Test Color Calibrate Sketch (Not tested)
2025-05-20 Color Calibration Debugged
2025-05-20 Added realignment after moving
2025-05-20 scanCube function started (not tested or debugged)
2025-05-21 Scan Cube Tested (Sensors not working?)
2025-05-21 Added servo partial retract
2025-05-28 Added median filter and updated partial servo retract
2025-06-11 Ring Partial Pos + Scan Cube Build + Solve Function
2025-08-05 Replaced MotorPots with MotorEncoders
    To Do:
    Test Motor Encoder code to verify if it works
    Update color sensor code for new color sensor boards
    Update all pins for new motherboard
2025-09-15 Added SolidWorks and KiCad files to repo
2025-09-15 Reorganized code directory structure
2025-09-16 Updated hardware pins, work on encoder mux, starting new color sensor code
2025-09-16 First draft for color sensors / encoders completed
2025-09-16 Minor ColorSensor debugging
2025-09-17 Motors confirmed working
2025-09-18 Verified mux+encoders work on small sketch
2025-10-11 New version of bottom motor assembly mostly designed
2025-10-12 Color Sensor Designed
2025-10-14 Color Sensor and Bottom Motor Assembly Full Design
2025-10-14 Remove cached files
2025-10-21 Color Sensor Working
2025-10-21 Color calibration potentially working!
2025-10-22 Bottom Motor CAD Finalized
2025-10-24 Reduced color sensor body height to reduce obstruction
2025-10-28 Cube Holders, Color Scan Debugging
2025-10-28 Color Sensor calibration and parsing working?
2025-10-28 SCAN AND SOLVE WORKING LETS GOOOOOO
2025-11-03 Initial Top Servo Track Redesign
2025-11-04 Top Frame Print
2025-11-11 Top Motor Assembly Printed
2025-11-13 Top Motor Assembly Revision
2025-11-18 Top Servo Installed and Working
2025-11-19 Solve with Button and Screen Working!
2025-11-22 Display Bracket Prototyped
2025-11-25 Forward Alignment Testing
2025-12-01 Display Panel Designed
2025-12-01 Integrated Cube Display
2025-12-02 Going back to test old code.
